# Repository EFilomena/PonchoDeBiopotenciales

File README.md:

# PonchoDeBiopotenciales

Este repositorio, contiene toda la información de desarrollo del poncho de adquisición de biopotenciales. 
Este poncho es parte del proyecto CIAA (http://www.proyecto-ciaa.com.ar/), y aplica fundamentalmente a la placa 
EDU-CIAA (http://www.proyecto-ciaa.com.ar/devwiki/doku.php?id=desarrollo:edu-ciaa:edu-ciaa-nxp). 

Permite la digitalización y registro de todo tipo de biopotenciales como: electrocardiograma, 
electroencefalograma, electromiograma, electrooculograma entre otros.

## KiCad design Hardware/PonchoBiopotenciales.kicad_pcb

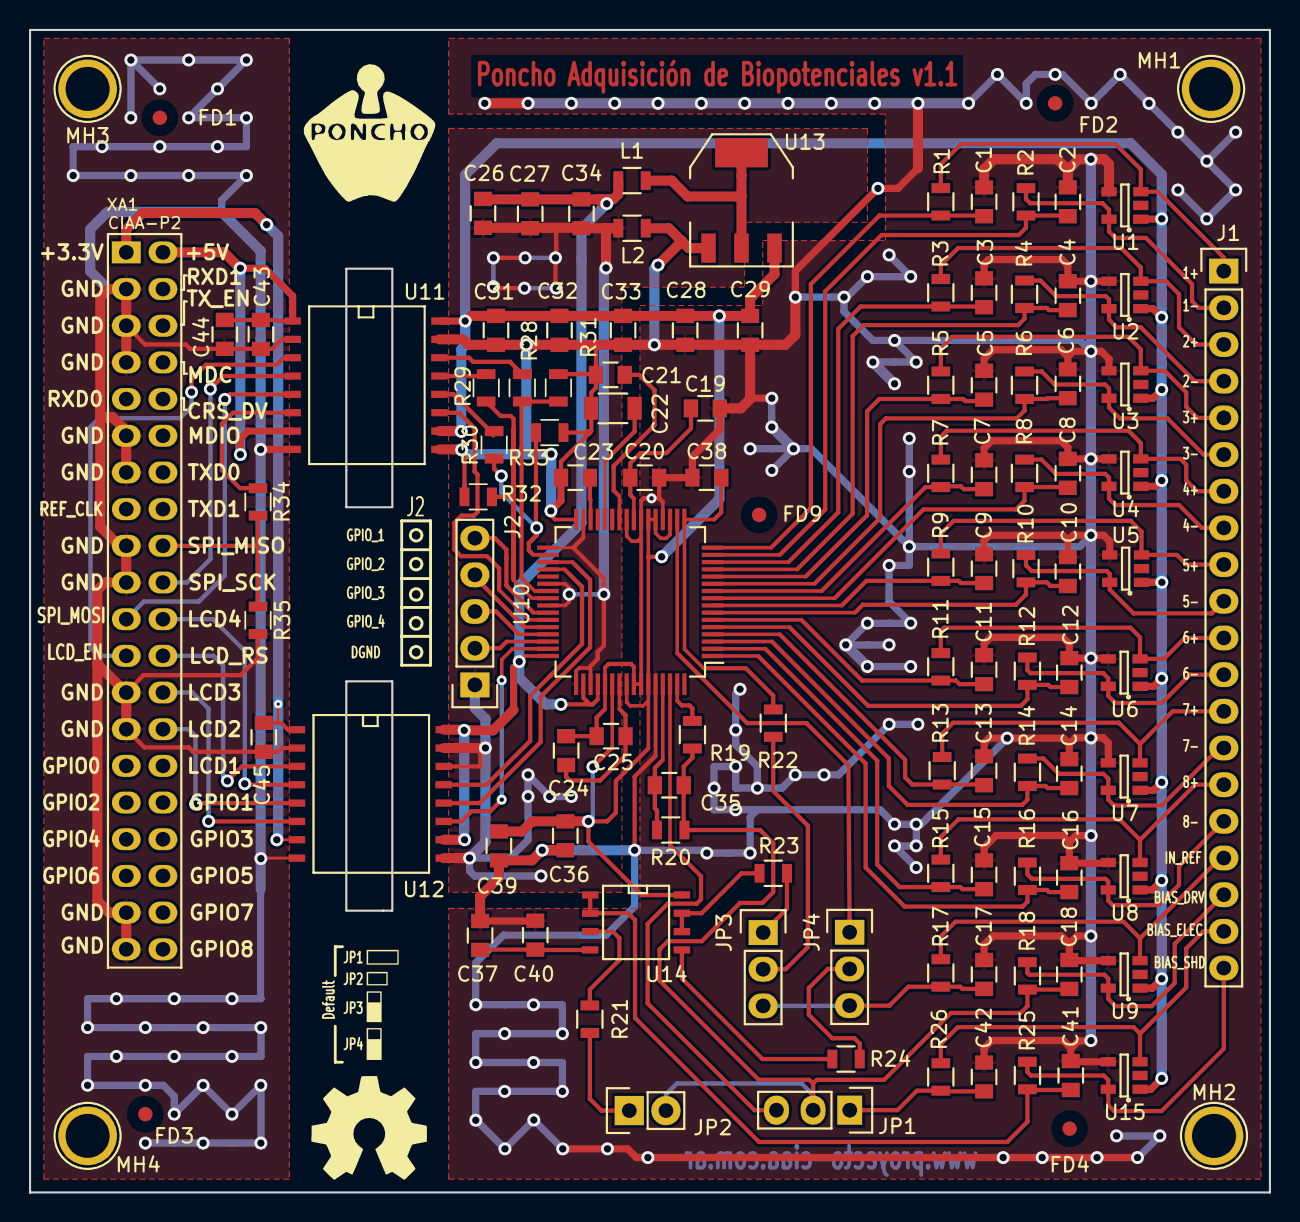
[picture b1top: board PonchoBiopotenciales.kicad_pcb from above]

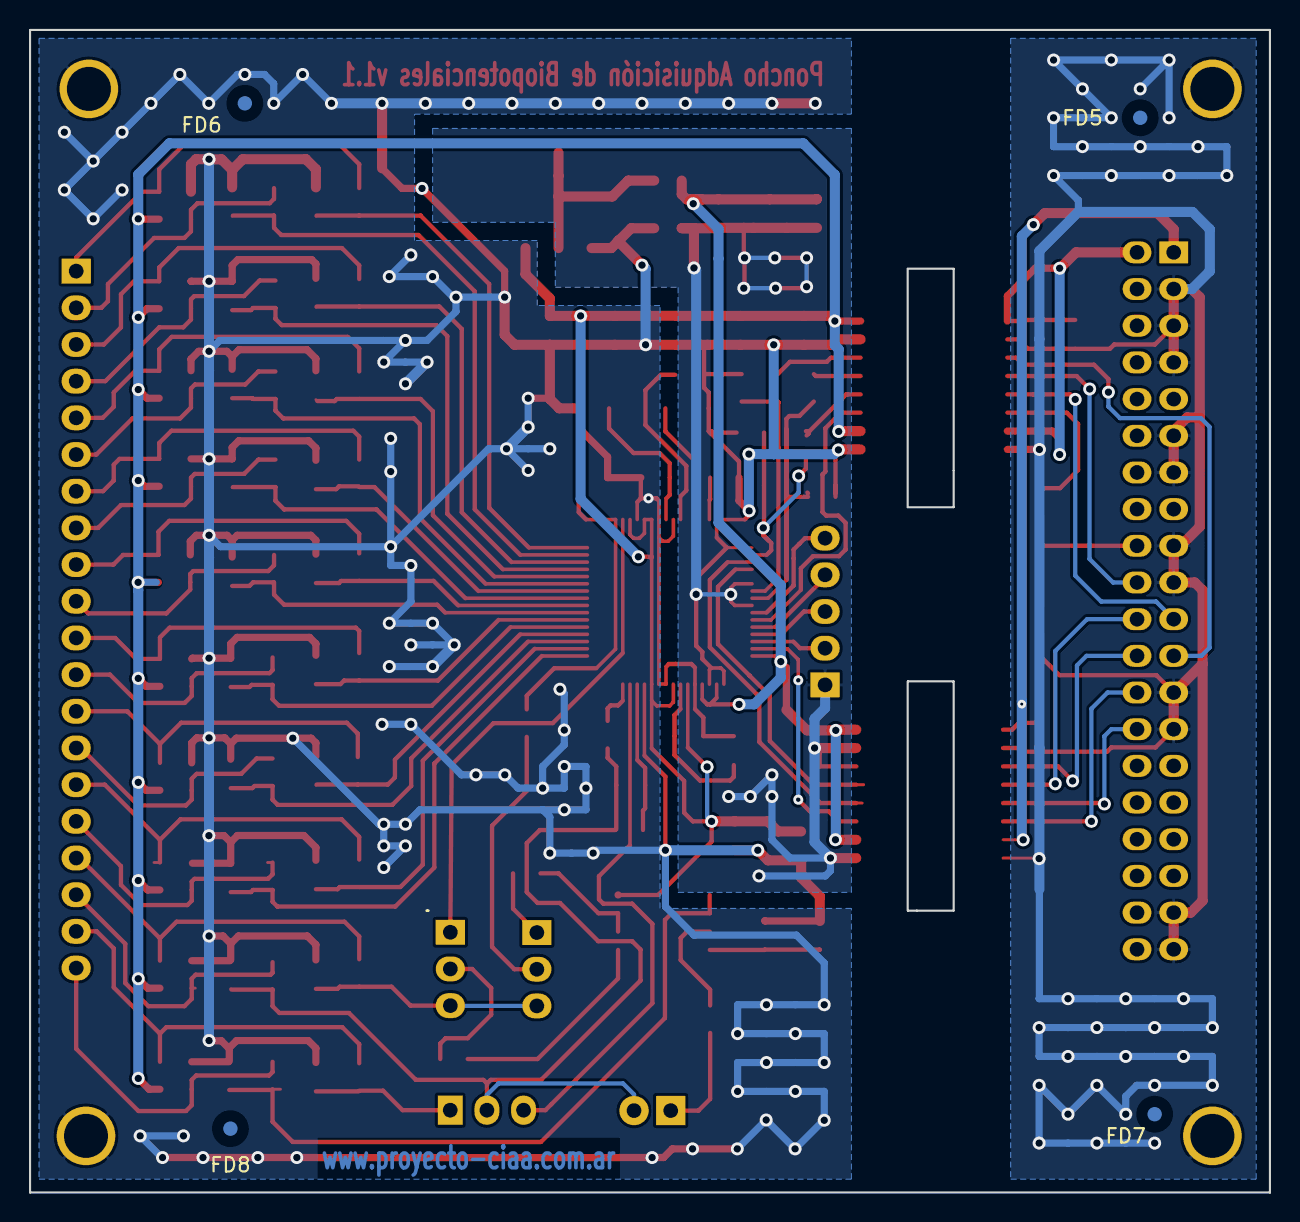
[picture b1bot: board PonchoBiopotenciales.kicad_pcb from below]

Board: 2 copper layers, 85.9 x 80.5 mm, 118 parts (4 on the bottom side), 89 nets.

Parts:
C1, C2, C3, C4, C5, C6, C7, C8, C9, C10, C11, C12, C13, C14, C15, C16, C17, C18, C38, C41, C42: 1nF; C_0805
C19, C24, C26, C28, C31, C43, C45: 0.1uF; C_0805
C20, C32, C33, C34, C44: 10uF; C_0805
C21, C23, C25, C27, C29, C36, C37, C39, C40: 1uF; C_0805
C22: 100uF; C_1206
C35: 0.01uF; C_0805
FD1, FD2, FD3, FD4, FD5, FD6, FD7, FD8, FD9: Fiducial; Fiducial_1mm_Dia_2.54mm_Outer_CopperTop
G1: Logo_Poncho
G2: OSHWA; Logo_OSHWA
J1: Entradas Analógicas; Pin_Header_Straight_1x20
J2: IOs Multipropósito; Pin_Header_Straight_1x05
JP1, JP3, JP4: JUMPER3; Pin_Header_Straight_1x03
JP2: JUMPER; Pin_Header_Straight_1x02
Jumper_STD1: J_STD; Jumpers_Default
L1, L2: HZ0805E601R-10; R_0805
MH1, MH2, MH3, MH4: PCB_HOLE; 1pin
R1, R2, R3, R4, R5, R6, R7, R8, R9, R10, R11, R12, R13, R14, R15, R16, R17, R18, R25, R26: 2.2k; R_0805
R19, R22, R23, R24: 0; R_0805
R20: 390k; R_0805
R21: 10k; R_0805
R28, R29, R30, R34: 1k; R_0805
R31, R32, R33, R35: 1.8k; R_0805
U1, U2, U3, U4, U5, U6, U7, U8, U9, U15: TPD2E001; SOT-23-5
U10: ADS1299; TQFP-64_10x10mm_Pitch0.5mm
U11: ADuM6401; SO-16-W
U12: ADuM2401; SO-16-W
U13: NCP1117ST33T3G; SOT-223
U14: OPA2376; SOIC-8-N
XA1: Conn_Poncho2P_2x_20x2; Conn_Poncho_Izquierdo

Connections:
+3.3V: C26.1, C27.1, C34.1, L1.1, U10.48, U10.50, U10.52, U12.10, U12.16
+5VA: C28.1, C29.1, C31.1, C32.1, C33.1, C36.1, C39.1, U1.1, U2.1, U3.1, U4.1, U5.1, U6.1, U7.1, U8.1, U9.1, U10.19, U10.21, U10.22, U10.54, U10.56, U10.59, U11.10, U11.16, U13.3, U14.8, U15.1
/ADS1299/BIAS_DRV: C18.1, C35.1, JP1.2, JP2.2, R18.1, R19.1, R20.1
/ADS1299/BIAS_ELEC: C42.1, JP1.1, R26.2
/ADS1299/BIAS_SHD: C41.1, R25.2, U14.1, U14.2
/ADS1299/CS/: R28.1, R31.2, U10.39
/ADS1299/DRDY/: U10.47, U12.11
/ADS1299/IN1+: C1.1, R1.2, U10.16
/ADS1299/IN1-: C2.1, R2.1, U10.15
/ADS1299/IN2+: C3.1, R3.1, U10.14
/ADS1299/IN2-: C4.1, R4.1, U10.13
/ADS1299/IN3+: C5.1, R5.2, U10.12
/ADS1299/IN3-: C6.1, R6.1, U10.11
/ADS1299/IN4+: C7.1, R7.1, U10.10
/ADS1299/IN4-: C8.1, R8.1, U10.9
/ADS1299/IN5+: C9.1, R9.2, U10.8
/ADS1299/IN5-: C10.1, R10.1, U10.7
/ADS1299/IN6+: C11.1, R11.1, U10.6
/ADS1299/IN6-: C12.1, R12.1, U10.5
/ADS1299/IN7+: C13.1, R13.2, U10.4
/ADS1299/IN7-: C14.1, R14.1, U10.3
/ADS1299/IN8+: C15.1, R15.1, U10.2
/ADS1299/IN8-: C16.1, R16.1, U10.1
/ADS1299/IN_REF: C17.1, JP3.3, JP4.3, R17.2
/ADS1299/MISO: U10.43, U11.11
/ADS1299/MOSI: R30.1, R33.2, U10.34
/ADS1299/PWDN/: U10.35, U12.12
/ADS1299/RESET: U10.36, U12.13
/ADS1299/SCLK: R29.1, R32.2, U10.40
/AISLACIÓN/+3.3V_NISO: C45.2, U12.1, U12.7, XA1.41
/AISLACIÓN/+5V_NISO: C43.1, C44.1, U11.1, U11.7, XA1.42
/AISLACIÓN/GND_NISO: C43.2, C44.2, C45.1, MH3.1, MH4.1, R35.1, U11.2, U11.8, U12.2, U12.8, XA1.43, XA1.45, XA1.47, XA1.51, XA1.53, XA1.57, XA1.59, XA1.65, XA1.67, XA1.77, XA1.79
/AISLACIÓN/_CS/: U11.3, XA1.63
/AISLACIÓN/_DRDY/: U12.6, XA1.66
/AISLACIÓN/_MISO: R34.2, R35.2, XA1.58
/AISLACIÓN/_MOSI: U11.5, XA1.61
/AISLACIÓN/_PWDN/: U12.5, XA1.68
/AISLACIÓN/_RESET: U12.4, XA1.62
/AISLACIÓN/_SCLK: U11.4, XA1.60
/AISLACIÓN/_START: U12.3, XA1.64
DGND: C26.2, C27.2, C34.2, J2.1, L2.1, U10.31, U10.33, U10.38, U10.41, U10.49, U10.51, U12.9, U12.14, U12.15
GNDA: C1.2, C2.2, C3.2, C4.2, C5.2, C6.2, C7.2, C8.2, C9.2, C10.2, C11.2, C12.2, C13.2, C14.2, C15.2, C16.2, C17.2, C18.2, C19.2, C20.2, C21.2, C22.2, C23.2, C24.2, C25.2, C28.2, C29.2, C31.2, C32.2, C33.2, C36.2, C37.2, C38.2, C39.2, C40.1, C41.2, C42.2, L2.2, MH1.1, MH2.1, R31.1, R32.1, R33.1, U1.4, U2.4, U3.4, U4.4, U5.4, U6.4, U7.4, U8.4, U9.4, U10.20, U10.23, U10.25, U10.32, U10.53, U10.57, U10.58, U10.60, U11.9, U11.15, U13.1, U15.4
unnamed: C19.1, C20.1, U10.24
unnamed: C21.1, U10.26
unnamed: C22.1, U10.28
unnamed: C23.1, U10.30
unnamed: C24.1, C25.1, U10.55
unnamed: C35.2, R20.2, U10.61
unnamed: C37.1, C40.2, U14.4
unnamed: C38.1, R22.2, U10.17
unnamed: J1.1, R1.1, U1.3
unnamed: J1.2, R2.2, U1.5
unnamed: J1.3, R3.2, U2.3
unnamed: J1.4, R4.2, U2.5
unnamed: J1.5, R5.1, U3.3
unnamed: J1.6, R6.2, U3.5
unnamed: J1.7, R7.2, U4.3
unnamed: J1.8, R8.2, U4.5
unnamed: J1.9, R9.1, U5.3
unnamed: J1.10, R10.2, U5.5
unnamed: J1.11, R11.2, U6.3
unnamed: J1.12, R12.2, U6.5
unnamed: J1.13, R13.1, U7.3
unnamed: J1.14, R14.2, U7.5
unnamed: J1.15, R15.2, U8.3
unnamed: J1.16, R16.2, U8.5
unnamed: J1.17, R17.1, U9.3
unnamed: J1.18, R18.2, U9.5
unnamed: J1.19, R26.1, U15.3
unnamed: J1.20, R25.1, U15.5
unnamed: J2.2, U10.46
unnamed: J2.3, U10.45
unnamed: J2.4, U10.44
unnamed: J2.5, U10.42
unnamed: JP1.3, U10.62
unnamed: JP2.1, R21.2
unnamed: JP3.1, R23.2
unnamed: JP3.2, R22.1
unnamed: JP4.1, U10.18
unnamed: JP4.2, R24.1
unnamed: L1.2, U13.2, U13.4
unnamed: R19.2, U10.63
unnamed: R21.1, U14.3
unnamed: R23.1, U14.6, U14.7
unnamed: R24.2, U14.5
unnamed: R28.2, U11.14
unnamed: R29.2, U11.13
unnamed: R30.2, U11.12
unnamed: R34.1, U11.6

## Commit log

2018-01-19 commit inicial de la placa PCB
2018-01-21 agregado de archivos de fabricación
2018-01-22 primer version del firmware
2018-01-22 gitignore modificado
2018-01-22 se añadió la librería faltante
2018-01-22 se borró archivo cachelib
2018-01-27 BOMs agregados
2018-01-28 Listado de materiales con precios DIGIKEY 01/2018
2018-01-28 README.md actualizado
2021-04-17 corregidos los slots de los ADUM
